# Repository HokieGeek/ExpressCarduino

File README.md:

# ExpressCardiuno 
My attempt to get some usefulness out of unused ports on my laptop by making use of the [ExpressCard slot](http://www.usb.org/developers/expresscard/EC_specifications/ExpressCard_2_0_FINAL.pdf) and adapting it to have [Adafruit's Metro Mini Arduino clone](https://www.adafruit.com/products/2590)

## Schematic and board

### Parts list

#### ICs
* [AP3012](http://www.mouser.com/ds/2/115/AP3012-271556.pdf) - Voltage regulator for USB 9v
* [SN74LV4051]() - 8ch analog multiplexer
* [MCP23017]() - 16bit I<sup>2</sup>C I/O expander

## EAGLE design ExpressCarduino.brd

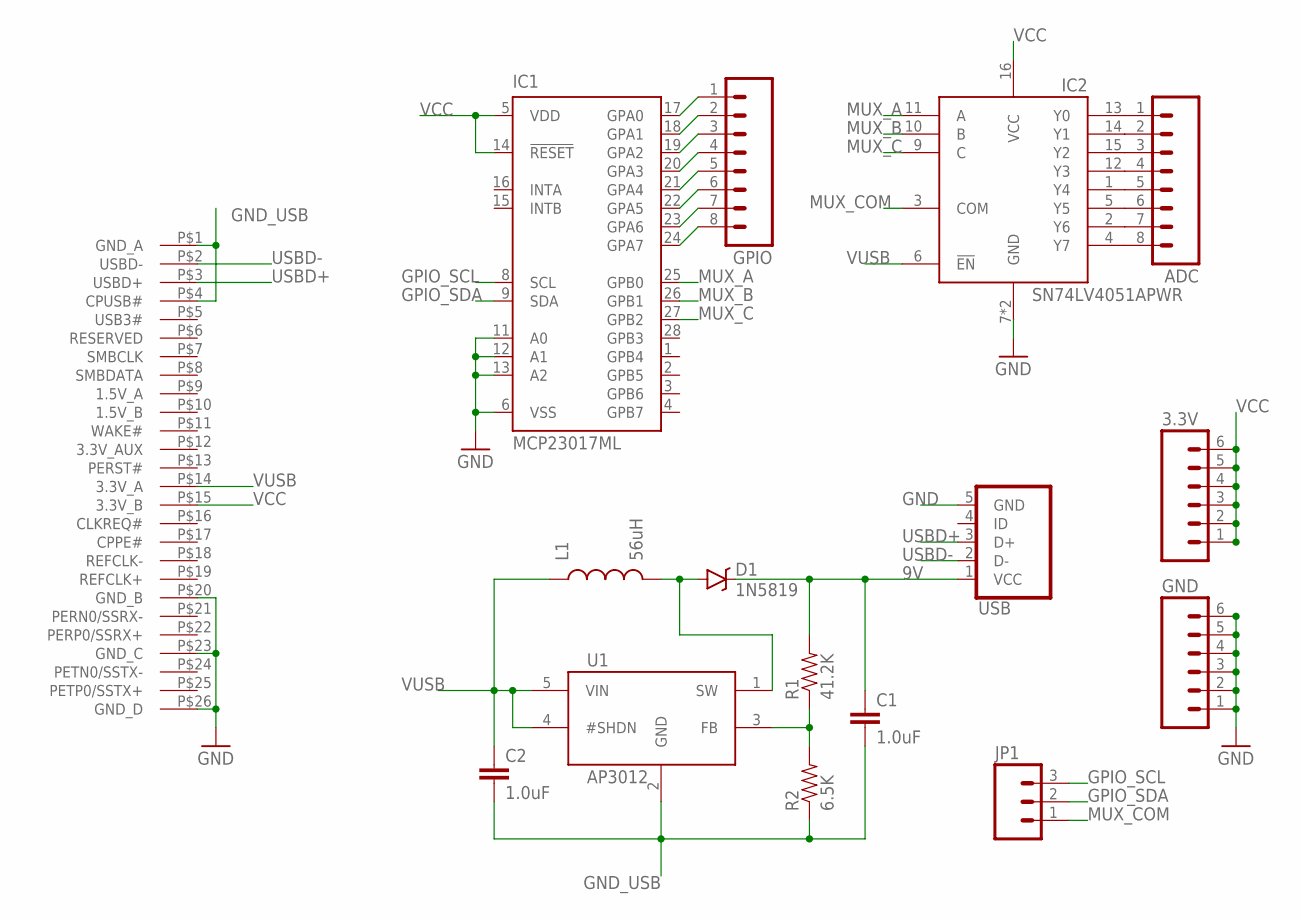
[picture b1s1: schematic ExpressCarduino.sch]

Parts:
3.3V: M06SILK_FEMALE_PTH; 1X06
ADC: M08; 1X08_ROUND
C1, C2: 1.0uF; 0603-CAP
D1: 1N5819; SOD-123
GND: M06SILK_FEMALE_PTH; 1X06
GPIO: M08; 1X08_ROUND
IC1: MCP23017ML; QFN28-ML_6X6MM
IC2: SN74LV4051APWR; TSSOP16
JP1: M03PTH; 1X03
L1: 56uH; SDR0403
R1: 41.2K; 0805
R2: 6.5K; 0805
U1: AP3012; SOT23-5
U$1: EXPRESSCARD34
USB: USB_MICROB_PLUG"; MICRO-B-RA-SMT

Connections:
9V: C1.1, D1.C, R1.2, USB.1 (VCC)
GND: GND.1, GND.2, GND.3, GND.4, GND.5, GND.6, IC1.6 (VSS), IC1.11 (A0), IC1.12 (A1), IC1.13 (A2), IC2.7 (GND), IC2.8 (GND), U$1.P$20 (GND_B), U$1.P$23 (GND_C), U$1.P$26 (GND_D), USB.5 (GND)
GND_USB: C1.2, C2.2, R2.1, U1.2 (GND), U$1.P$1 (GND_A), U$1.P$4 (CPUSB#)
GPIO_SCL: IC1.8 (SCL), JP1.3
GPIO_SDA: IC1.9 (SDA), JP1.2
MUX_A: IC1.25 (GPB0), IC2.11 (A)
MUX_B: IC1.26 (GPB1), IC2.10 (B)
MUX_C: IC1.27 (GPB2), IC2.9 (C)
MUX_COM: IC2.3 (COM), JP1.1
unnamed: R1.1, R2.2, U1.3 (FB)
unnamed: GPIO.1, IC1.17 (GPA0)
unnamed: D1.A, L1.P$2 (2), U1.1 (SW)
unnamed: GPIO.2, IC1.18 (GPA1)
unnamed: GPIO.3, IC1.19 (GPA2)
unnamed: GPIO.4, IC1.20 (GPA3)
unnamed: GPIO.5, IC1.21 (GPA4)
unnamed: GPIO.6, IC1.22 (GPA5)
unnamed: GPIO.7, IC1.23 (GPA6)
unnamed: GPIO.8, IC1.24 (GPA7)
unnamed: ADC.1, IC2.13 (Y0)
unnamed: ADC.2, IC2.14 (Y1)
unnamed: ADC.3, IC2.15 (Y2)
unnamed: ADC.4, IC2.12 (Y3)
unnamed: ADC.5, IC2.1 (Y4)
unnamed: ADC.6, IC2.5 (Y5)
unnamed: ADC.7, IC2.2 (Y6)
unnamed: ADC.8, IC2.4 (Y7)
USBD+: U$1.P$3 (USBD+), USB.3 (D+)
USBD-: U$1.P$2 (USBD-), USB.2 (D-)
VCC: 3.3V.1, 3.3V.2, 3.3V.3, 3.3V.4, 3.3V.5, 3.3V.6, IC1.5 (VDD), IC1.14 (!RESET), IC2.16 (VCC), U$1.P$15 (3.3V_B)
VUSB: C2.1, IC2.6 (!EN), L1.P$1 (1), U1.4 (#SHDN), U1.5 (VIN), U$1.P$14 (3.3V_A)

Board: 2 copper layers, 16 parts (0 on the bottom side), 31 nets, no tracks yet.

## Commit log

2015-11-06 Initial layout
2015-11-08 Added vreg circuit for 3.3v -> 9v and images
2015-11-08 Updated readme with pictures!
2015-11-08 Whoops
2015-11-08 *sigh*
2015-11-09 Added the Mini USB part
2015-11-10 Ignore the pro files
2015-11-10 Added an IO expander and more ADC lines. Not sure why, tbh
2015-11-10 Added sample Arduino sketch and a makefile
2015-11-10 Isolated the USB circuit from the other ICs
2015-11-10 Added thoughts on sensors and such...
    should have probably been an issue instead...
2015-11-10 Zipping up two separate examples
2015-11-11 Updated with correct measurements for the USB plug and swaped out the 8bit expander for the 16
2015-11-11 Fixed pins for the mux and rearranged the board for better routing
2015-11-11 Minor tweaks
2015-11-11 I really have to go to bed
2015-11-11 I keep tweaking the board...
2015-11-11 Added the ICs
2015-11-12 Greatly refactored the samples I grabbed this from to suit my needs. Tested with Uno
2015-11-12 Stopped verifying on upload as it is redundant
2015-11-12 More tweaks
2015-11-13 Got the connection LED working
2015-11-13 Split up the sketch
2015-11-13 Added power supply pins based on #10
2015-11-18 Added ambient light sensors
2015-11-18 Trying things out
2015-11-25 Trying to configure this so that Travis-CI can build arduino
2015-11-25 Would be great if this worked...
2015-11-25 Typo
2015-11-25 Interesting
2015-11-25 Playing with Travis-CI
2015-11-25 Removed the potentiometer stuff since that was just for playing around
2015-11-25 Still trying to make this work with the new infrastructure, even if just a little bit
2015-11-25 Fleshing out the data being sent back over the serial line
2015-11-25 Moved ACK define to parrent sketch
2015-11-25 Using ACK define now
2015-12-01 Hopefully correctly added a relatively precise tmp36 reading
2015-12-05 Sending out bytes
2015-12-05 Changing the handshaking routine
2015-12-05 Learned I fucked up the TMP36 breakout. LOL!
2015-12-08 ohhhhh!
2018-08-06 Modified current schematic to remove potential nogo and added "basic" board

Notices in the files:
parts and their libraries:
SparkFun-Resistors: Licensing: Creative Commons ShareAlike 4.0 International - https://creativecommons.org/licenses/by-sa/4.0
